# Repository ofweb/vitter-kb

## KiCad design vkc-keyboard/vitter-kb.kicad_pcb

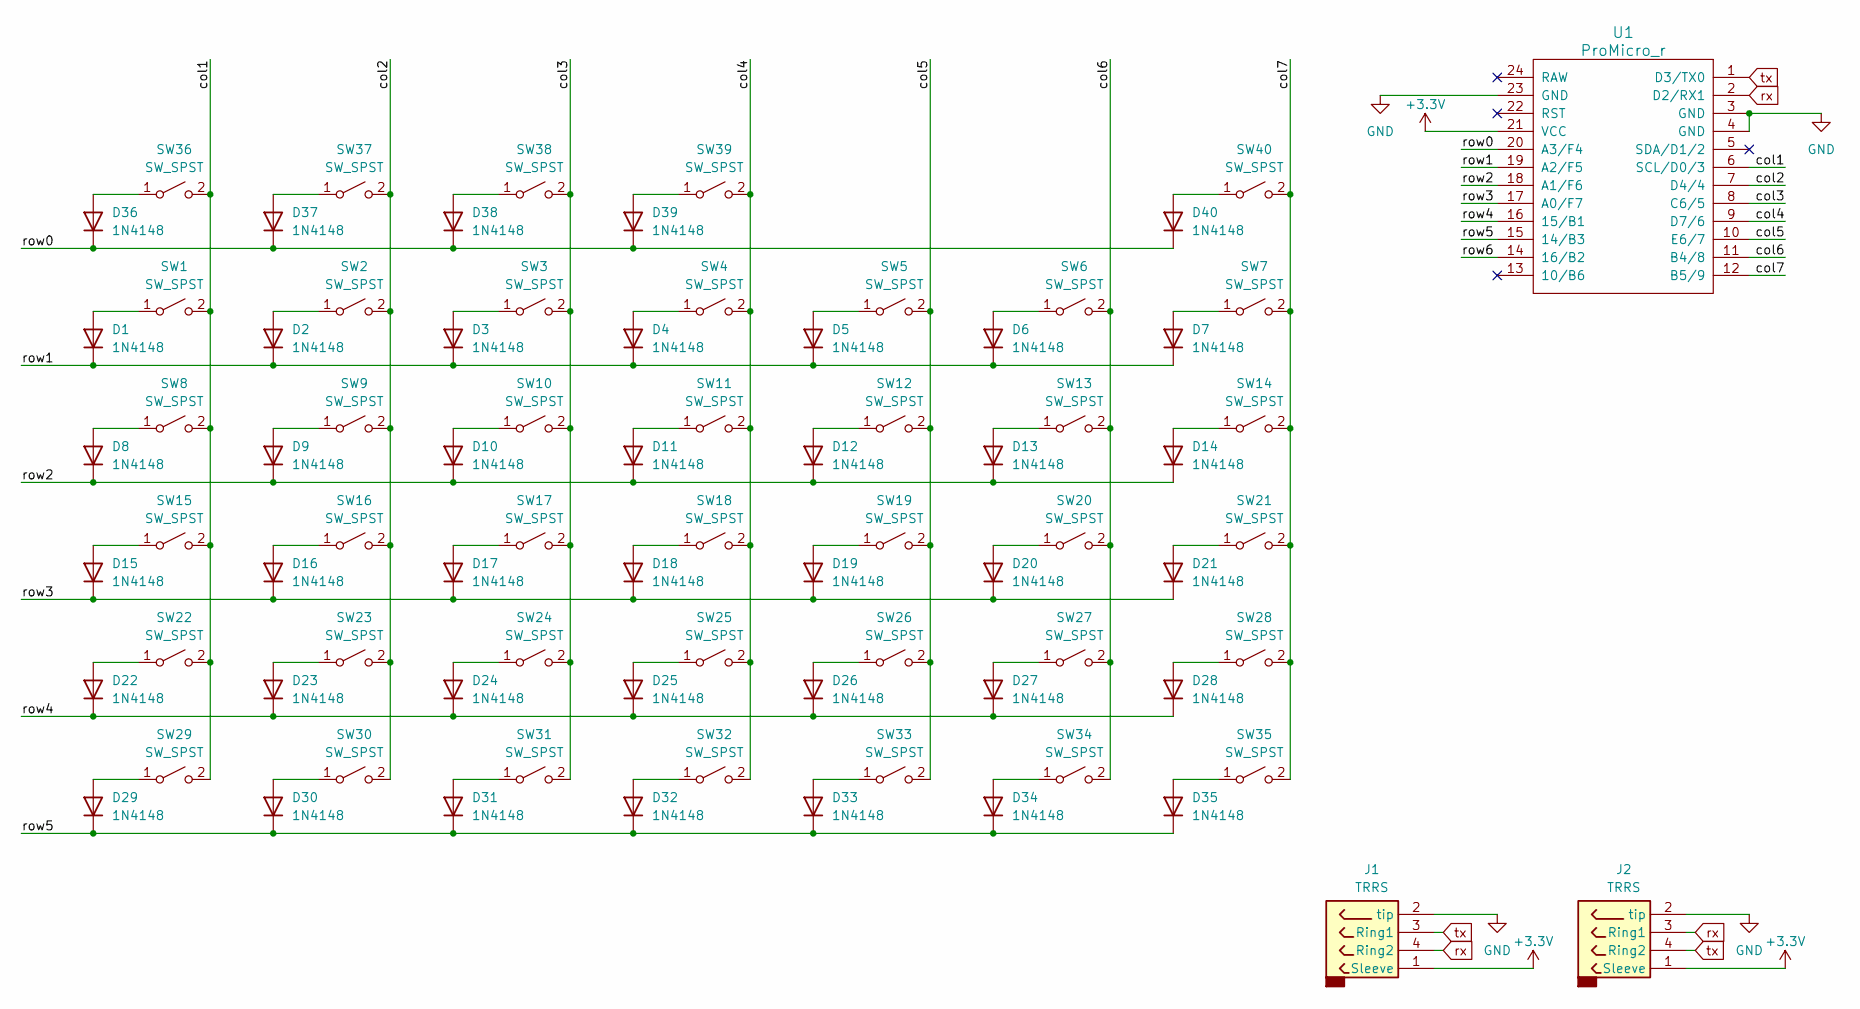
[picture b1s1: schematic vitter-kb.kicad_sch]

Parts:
D1, D2, D3, D4, D5, D6, D7, D8, D9, D10, D11, D12, D13, D14, D15, D16, D17, D18, D19, D20, D21, D22, D23, D24, D25, D26, D27, D28, D29, D30, D31, D32, D33, D34, D35, D36, D37, D38, D39, D40: 1N4148; Diode-SOD-123-FB
J1, J2: TRRS; TRRS-PJ-320A
SW1, SW2, SW3, SW4, SW5, SW6, SW7, SW8, SW9, SW10, SW11, SW12, SW13, SW14, SW15, SW16, SW17, SW18, SW19, SW20, SW21, SW22, SW23, SW24, SW25, SW26, SW27, SW28, SW29, SW30, SW31, SW32, SW33, SW34, SW35, SW36, SW37, SW38, SW39, SW40: SW_SPST; Kailh_socket_PG1350_reversible
U1: ProMicro_r; ProMicro_v2

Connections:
+3.3V: J1.1 (Sleeve), J2.1 (Sleeve), U1.21 (VCC)
/col1: SW1.2 (B), SW8.2 (B), SW15.2 (B), SW22.2 (B), SW29.2 (B), SW36.2 (B), U1.6 (SCL/D0/3)
/col2: SW2.2 (B), SW9.2 (B), SW16.2 (B), SW23.2 (B), SW30.2 (B), SW37.2 (B), U1.7 (D4/4)
/col3: SW3.2 (B), SW10.2 (B), SW17.2 (B), SW24.2 (B), SW31.2 (B), SW38.2 (B), U1.8 (C6/5)
/col4: SW4.2 (B), SW11.2 (B), SW18.2 (B), SW25.2 (B), SW32.2 (B), SW39.2 (B), U1.9 (D7/6)
/col5: SW5.2 (B), SW12.2 (B), SW19.2 (B), SW26.2 (B), SW33.2 (B), U1.10 (E6/7)
/col6: SW6.2 (B), SW13.2 (B), SW20.2 (B), SW27.2 (B), SW34.2 (B), U1.11 (B4/8)
/col7: SW7.2 (B), SW14.2 (B), SW21.2 (B), SW28.2 (B), SW35.2 (B), SW40.2 (B), U1.12 (B5/9)
/row0: D36.1 (K), D37.1 (K), D38.1 (K), D39.1 (K), D40.1 (K), U1.20 (A3/F4)
/row1: D1.1 (K), D2.1 (K), D3.1 (K), D4.1 (K), D5.1 (K), D6.1 (K), D7.1 (K), U1.19 (A2/F5)
/row2: D8.1 (K), D9.1 (K), D10.1 (K), D11.1 (K), D12.1 (K), D13.1 (K), D14.1 (K), U1.18 (A1/F6)
/row3: D15.1 (K), D16.1 (K), D17.1 (K), D18.1 (K), D19.1 (K), D20.1 (K), D21.1 (K), U1.17 (A0/F7)
/row4: D22.1 (K), D23.1 (K), D24.1 (K), D25.1 (K), D26.1 (K), D27.1 (K), D28.1 (K), U1.16 (15/B1)
/row5: D29.1 (K), D30.1 (K), D31.1 (K), D32.1 (K), D33.1 (K), D34.1 (K), D35.1 (K), U1.15 (14/B3)
/row6: U1.14 (16/B2)
GND: J1.2 (tip), J2.2 (tip), U1.3 (GND), U1.4 (GND), U1.23 (GND)
unnamed: D1.2 (A), SW1.1 (A)
unnamed: D2.2 (A), SW2.1 (A)
unnamed: D3.2 (A), SW3.1 (A)
unnamed: D4.2 (A), SW4.1 (A)
unnamed: D5.2 (A), SW5.1 (A)
unnamed: D6.2 (A), SW6.1 (A)
unnamed: D7.2 (A), SW7.1 (A)
unnamed: D8.2 (A), SW8.1 (A)
unnamed: D9.2 (A), SW9.1 (A)
unnamed: D10.2 (A), SW10.1 (A)
unnamed: D11.2 (A), SW11.1 (A)
unnamed: D12.2 (A), SW12.1 (A)
unnamed: D13.2 (A), SW13.1 (A)
unnamed: D14.2 (A), SW14.1 (A)
unnamed: D15.2 (A), SW15.1 (A)
unnamed: D16.2 (A), SW16.1 (A)
unnamed: D17.2 (A), SW17.1 (A)
unnamed: D18.2 (A), SW18.1 (A)
unnamed: D19.2 (A), SW19.1 (A)
unnamed: D20.2 (A), SW20.1 (A)
unnamed: D21.2 (A), SW21.1 (A)
unnamed: D22.2 (A), SW22.1 (A)
unnamed: D23.2 (A), SW23.1 (A)
unnamed: D24.2 (A), SW24.1 (A)
unnamed: D25.2 (A), SW25.1 (A)
unnamed: D26.2 (A), SW26.1 (A)
unnamed: D27.2 (A), SW27.1 (A)
unnamed: D28.2 (A), SW28.1 (A)
unnamed: D29.2 (A), SW29.1 (A)
unnamed: D30.2 (A), SW30.1 (A)
unnamed: D31.2 (A), SW31.1 (A)
unnamed: D32.2 (A), SW32.1 (A)
unnamed: D33.2 (A), SW33.1 (A)
unnamed: D34.2 (A), SW34.1 (A)
unnamed: D35.2 (A), SW35.1 (A)
unnamed: D36.2 (A), SW36.1 (A)
unnamed: D37.2 (A), SW37.1 (A)
unnamed: D38.2 (A), SW38.1 (A)
unnamed: D39.2 (A), SW39.1 (A)
unnamed: D40.2 (A), SW40.1 (A)
rx: J1.4 (Ring2), J2.3 (Ring1), U1.2 (D2/RX1)
tx: J1.3 (Ring1), J2.4 (Ring2), U1.1 (D3/TX0)

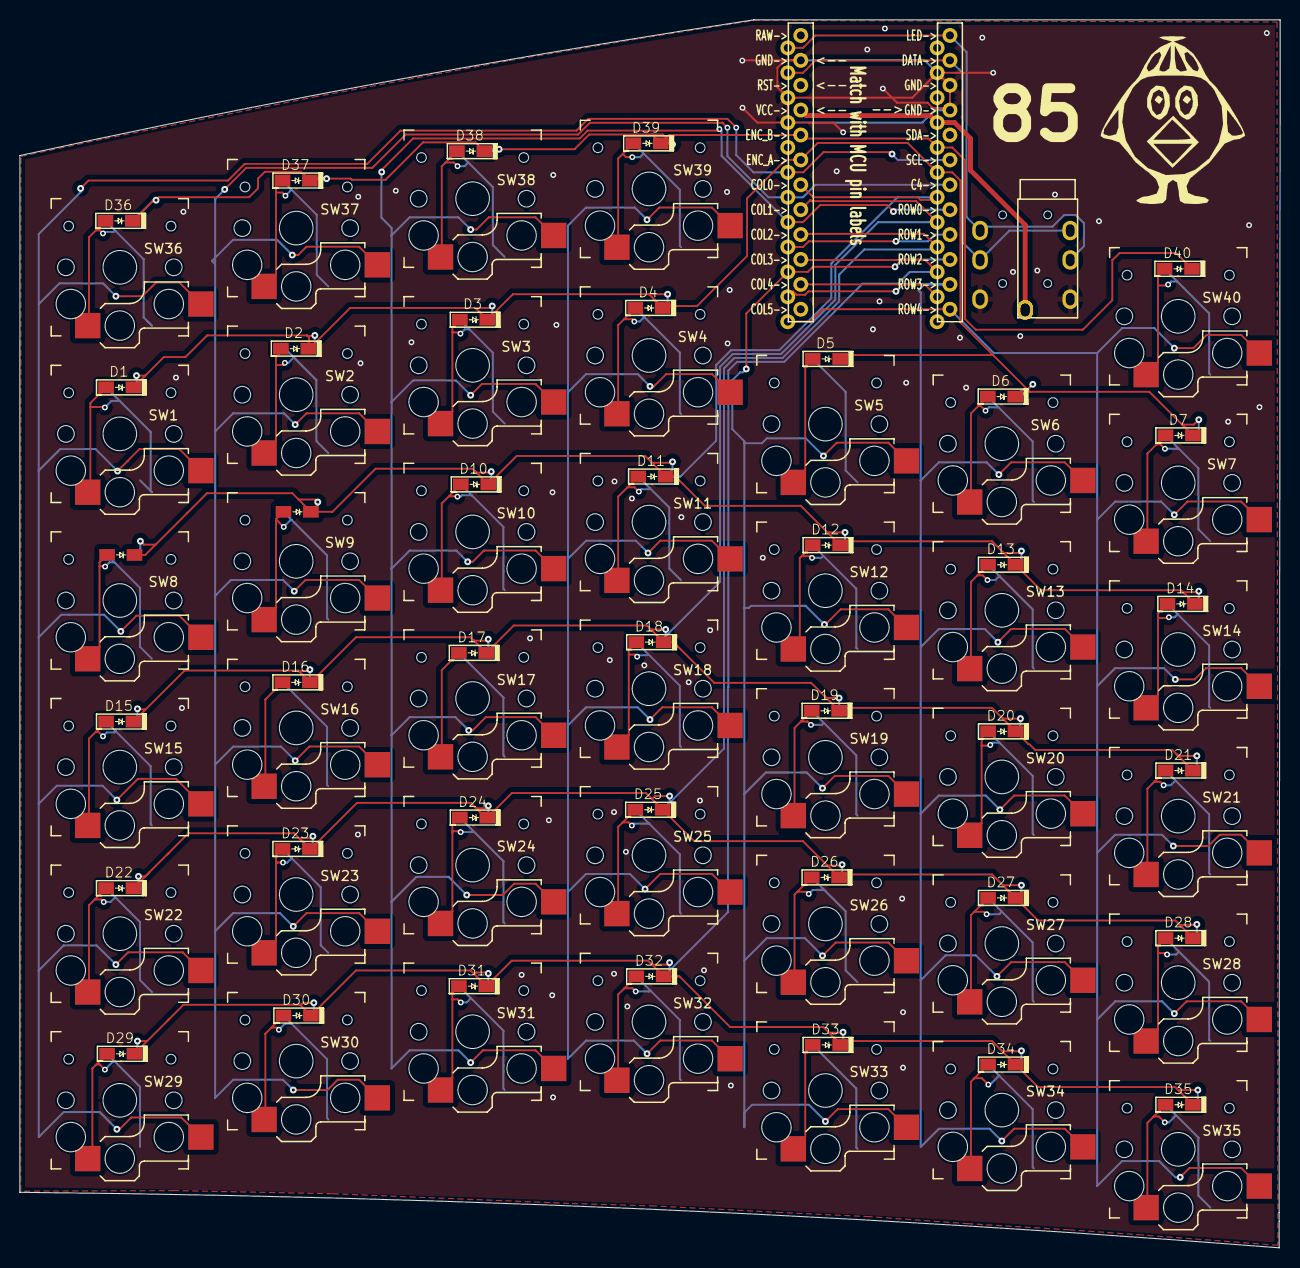
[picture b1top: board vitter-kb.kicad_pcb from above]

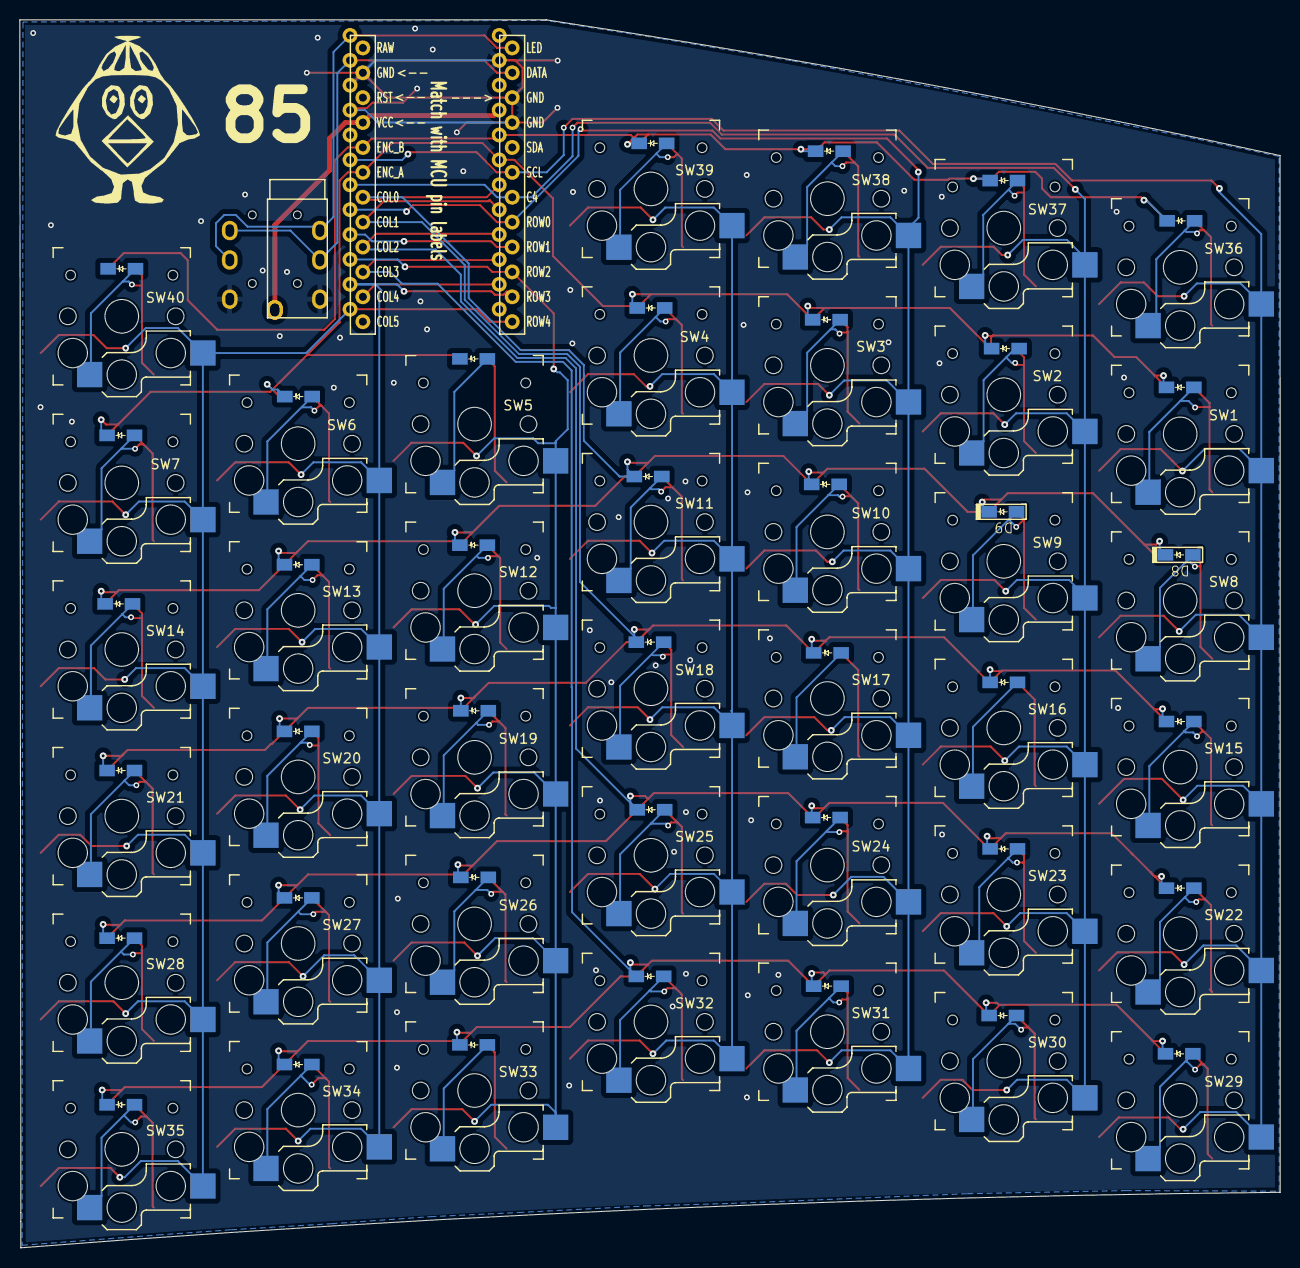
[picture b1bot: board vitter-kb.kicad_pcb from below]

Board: 2 copper layers, 128.6 x 125.3 mm, 83 parts (3 on the bottom side), 57 nets.

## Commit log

2024-10-31 Initial
2024-11-01 use button outline footprint
2024-11-04 bingo
2024-11-05 route
2024-11-05 add edge cut
2024-11-05 ryg venstre kolone og tre højre 2mm ned
2024-11-06 add gerber
2024-11-07 fix all DRC errors
